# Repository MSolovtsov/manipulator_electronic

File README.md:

# Электроника манипулятора для лабораторных работ

Подпроект «Электроника» проекта «Манипулятор для лабораторных работ». Подключён как Git submodule
к родительскому репозиторию `educational-manipulator`.

## Состав электроники

Архитектура: контроллер ESP32-S3 (связь с ПК по USB); четыре канала привода
M1…M4 в основании — коллекторные ДПТ 24 В с драйвером, реле отключения,
датчиком тока и I2C-энкодером через мультиплексор (M1 — поворот платформы,
M2…M4 — звенья через токосъёмное кольцо); съёмный схват M5 с собственной
электроникой по UART; два режима работы — полный (от ESP32) и лабораторный
(управление звеном с внешнего разъёма), переключаемые кнопкой KH; питание от
внешнего адаптера 24 В с гальванической развязкой логики от силовой части.

Конкретные компоненты, их статусы (утверждено / предложение / уточняется),
спорные пункты и цены — в базе компонентов **`bom/Component_Base.xlsx`**
(листы «Компоненты», «Модули», «Отклонено», «Сводка», «Справочники»).
Текстовые копии листов для просмотра диффов — `bom/csv/`, обновляются
скриптом `scripts/export_component_base.py`.

Не определены: число степеней свободы, грузоподъёмность, двигатели, состав и
число плат. Исходные данные — концепт на доске Miro.

| Плата | Назначение | Кол-во | Текущая ревизия |
|-------|-----------|--------|-----------------|
| CH | Плата силовой части: развязка, драйвер, реле отключения, датчик тока, реле режима | 4 | — |
| MC | Плата микроконтроллера: ESP32-S3, мультиплексор I2C, оптореле KH, концевик M1, UART схвата, разъёмы CH | 1 | — |
| PS | Плата питания: реле шины 24 В, TVS, XL4015E, изолированный DC-DC острова, раздача +24 | 1 | — |
| LR | Плата режима ЛР: клеммы M1…M4, защита, PCF8574 и индикаторы звеньев | 1 | — |
| GR | Электроника схвата (по ТЗ на схват) | 1 | — |

Обоснование разделения, состав и связи между платами —
`docs/board-partition.md`. Плата CH проектируется после выбора двигателя
(от него зависят драйвер и реле отключения); MC, PS и LR — не ждут.

## Структура репозитория

```
electronics/
├── lib/            общие библиотеки KiCad для всех плат
│   ├── symbols/    символы (*.kicad_sym)
│   ├── footprints/ посадочные места (*.pretty/)
│   └── 3dmodels/   3D-модели компонентов (*.step, *.wrl) — только используемые в проекте
├── boards/         KiCad-проекты; один каталог = одна плата
│   └── <плата>/
│       └── release/<rev>/   замороженные выходные файлы изготовленной ревизии
├── system/         уровень системы: структурная схема, распиновка разъёмов
│   └── wiring/     схема соединений между платами, жгуты, кабели
├── calc/           расчёты: питание, токи, тепловой режим
├── bom/            база компонентов Component_Base.xlsx + csv/ для диффов
├── docs/           обоснование выбора приводов, датчиков, контроллера
└── scripts/        скрипты экспорта и проверки (export_component_base.py)
```

В репозиторий попадают исходники KiCad (`*.kicad_pro`, `*.kicad_sch`, `*.kicad_pcb`),
таблицы библиотек проекта (`sym-lib-table`, `fp-lib-table`), содержимое `lib/` и
каталоги `release/`. Резервные копии, автосохранения, локальные настройки вида
и пересоздаваемые выходные файлы (Gerber, отчёты DRC/ERC) не хранятся — см. `.gitignore`.

## Инструменты

- KiCad: **10.0**. Форматы файлов между мажорными версиями несовместимы,
  поэтому все участники работают в одной мажорной версии; она фиксируется здесь
  и не меняется в течение ревизии платы.
- `kicad-cli` — для экспорта схем, BOM и Gerber из скриптов в `scripts/`.

## Как открыть проект

Открыть `boards/<плата>/<плата>.kicad_pro` в KiCad. Библиотеки подключены через
таблицы проекта относительным путём `${KIPRJMOD}/../../lib/...`, глобальная
настройка путей не требуется.

Если KiCad сообщает об отсутствующих библиотеках:
1. проверить, что репозиторий склонирован целиком и каталог `lib/` не пуст;
2. проверить, что проект открыт из своего каталога в `boards/`, а не из копии;
3. убедиться, что версия KiCad соответствует указанной в разделе «Инструменты».

## Ревизии и выпуск

Ревизия платы записывается в поле `Rev` титульного блока схемы и выносится на
шёлкографию платы. Формат: `<код платы>-<ревизия>`, например `MC-A1`; код платы
задаётся при создании проекта платы.

На каждую ревизию, отправленную в производство, ставится Git-тег вида
`<плата>/<ревизия>`. Родительский репозиторий фиксирует коммит этого подпроекта,
поэтому по тегу родительского репозитория однозначно восстанавливается набор
ревизий всех плат конкретной версии манипулятора.

В `boards/<плата>/release/<rev>/` сохраняются выходные файлы изготовленной ревизии:
Gerber и drill, BOM, файл позиций компонентов, PDF схемы. Они соответствуют
физически существующей плате и не пересоздаются. Экспорт выполняется скриптом
из `scripts/` (команда уточняется после появления скрипта).

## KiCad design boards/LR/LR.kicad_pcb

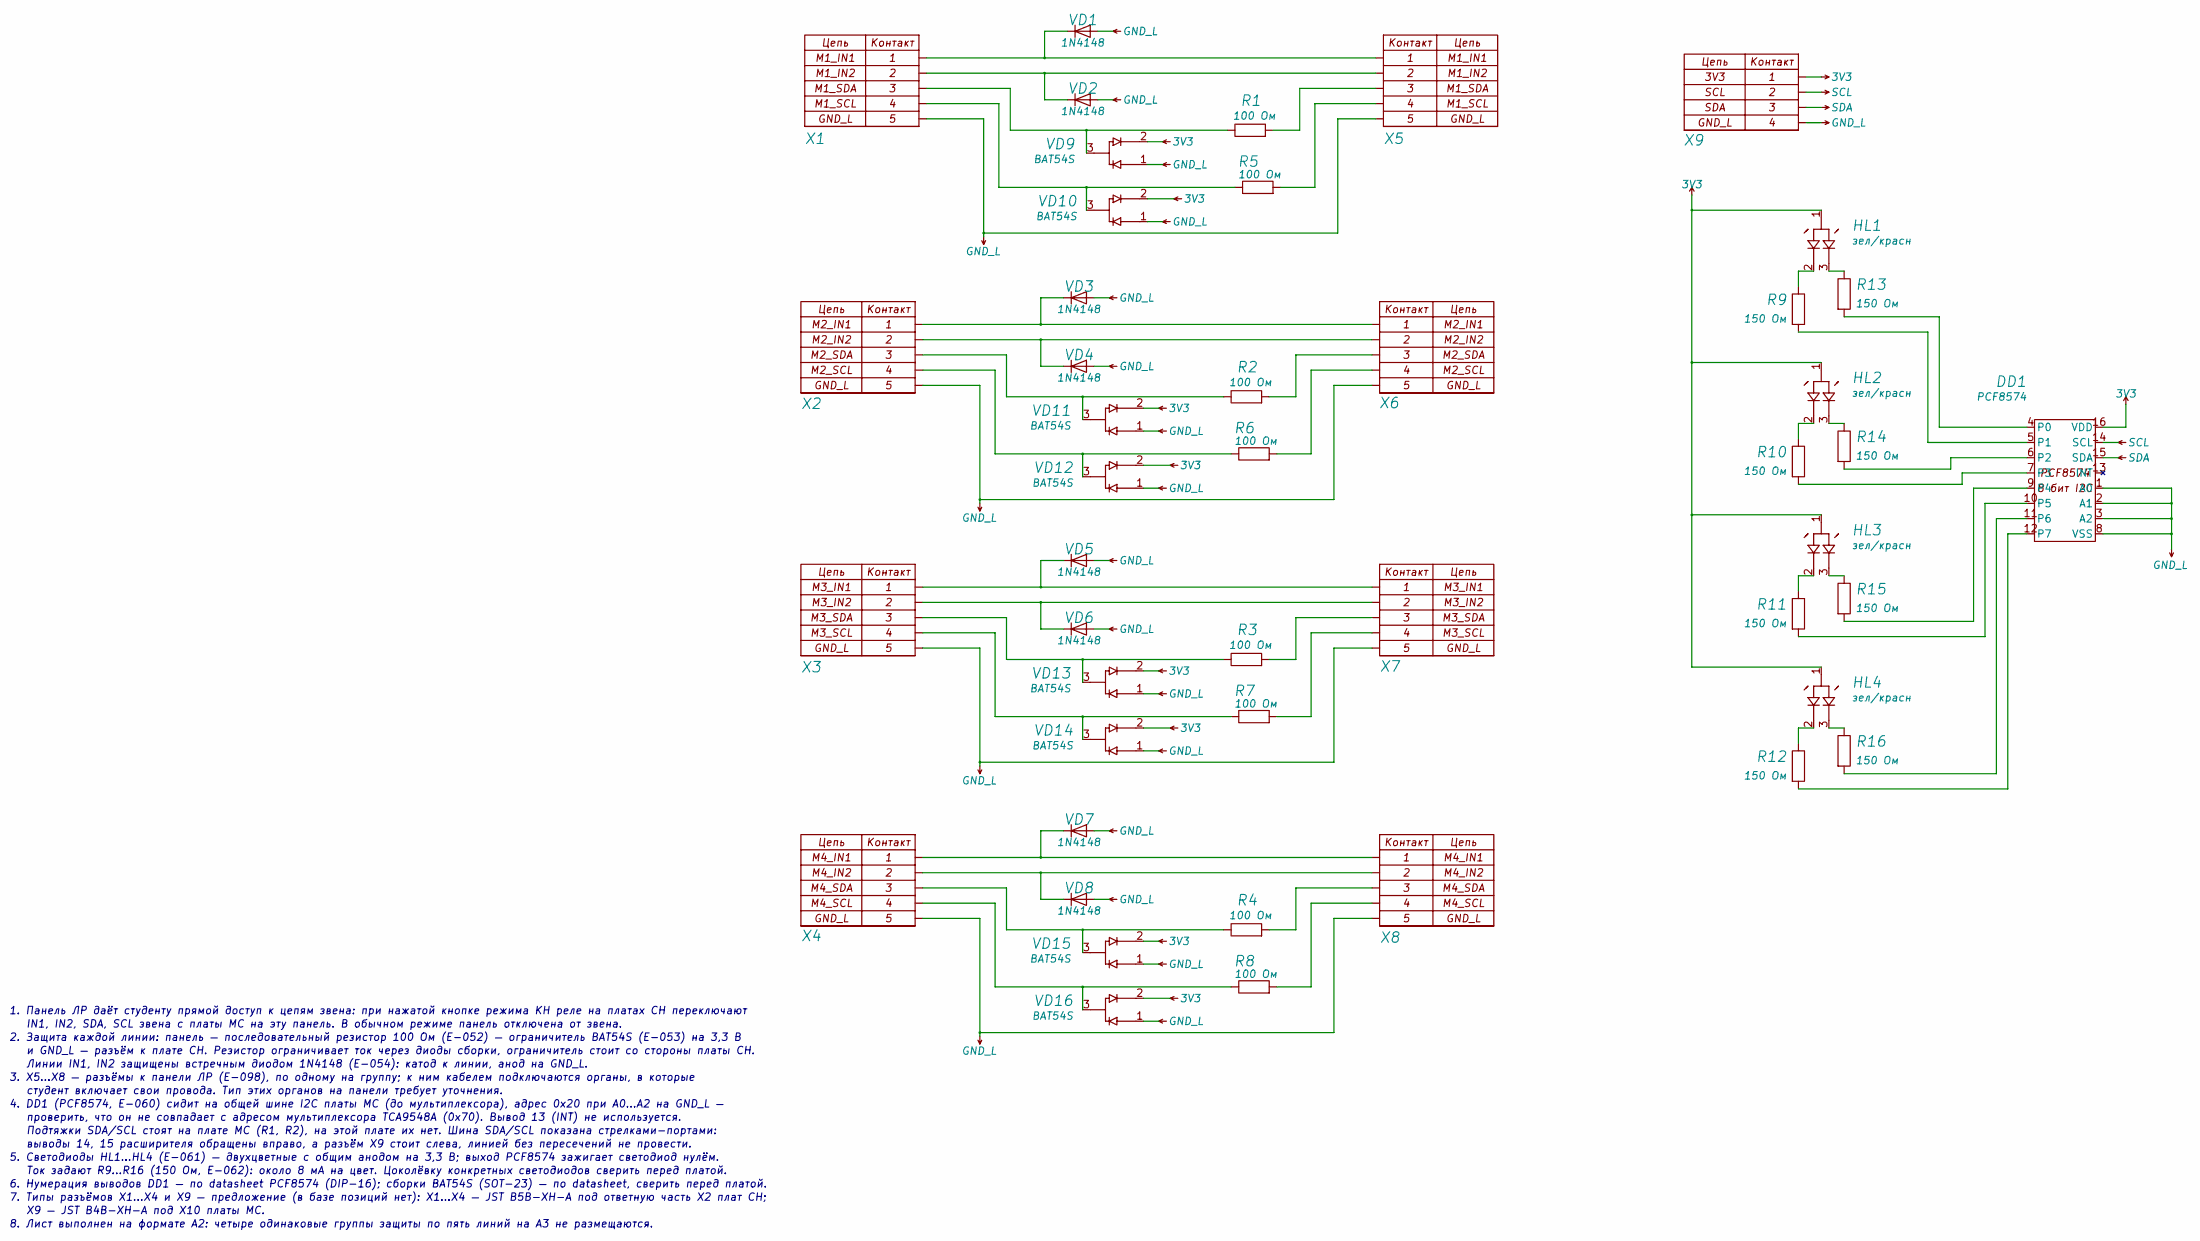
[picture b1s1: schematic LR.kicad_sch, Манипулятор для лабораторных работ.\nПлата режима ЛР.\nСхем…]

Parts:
DD1: PCF8574; DIP-16_W7.62mm
HL1, HL2, HL3, HL4: зел/красн; LED_Bicolor_5mm
R1, R2, R3, R4, R5, R6, R7, R8: 100 Ом; R_Axial_P10.16mm_V
R9, R10, R11, R12, R13, R14, R15, R16: 150 Ом; R_Axial_P10.16mm_V
VD1, VD2, VD3, VD4, VD5, VD6, VD7, VD8: 1N4148; D_DO-35_P7.62mm
VD9, VD10, VD11, VD12, VD13, VD14, VD15, VD16: BAT54S; SOT-23
X1, X2, X3, X4, X5, X6, X7, X8: B5B-XH-A; JST_XH_B5B-XH-A_L
X9: B4B-XH-A; JST_XH_B4B-XH-A_R

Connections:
3V3: DD1.16 (VDD), HL1.1 (A), HL2.1 (A), HL3.1 (A), HL4.1 (A), VD9.2 (K), VD10.2 (K), VD11.2 (K), VD12.2 (K), VD13.2 (K), VD14.2 (K), VD15.2 (K), VD16.2 (K), X9.1 (3V3)
GND_L: DD1.1 (A0), DD1.2 (A1), DD1.3 (A2), DD1.8 (VSS), VD1.2 (A), VD2.2 (A), VD3.2 (A), VD4.2 (A), VD5.2 (A), VD6.2 (A), VD7.2 (A), VD8.2 (A), VD9.1 (A), VD10.1 (A), VD11.1 (A), VD12.1 (A), VD13.1 (A), VD14.1 (A), VD15.1 (A), VD16.1 (A), X1.5 (GND_L), X2.5 (GND_L), X3.5 (GND_L), X4.5 (GND_L), X5.5 (GND_L), X6.5 (GND_L), X7.5 (GND_L), X8.5 (GND_L), X9.4 (GND_L)
unnamed: DD1.4 (P0), R13.2
unnamed: DD1.5 (P1), R9.2
unnamed: DD1.6 (P2), R14.2
unnamed: DD1.7 (P3), R10.2
unnamed: DD1.9 (P4), R15.2
unnamed: DD1.10 (P5), R11.2
unnamed: DD1.11 (P6), R16.2
unnamed: DD1.12 (P7), R12.2
unnamed: HL1.2 (K1), R9.1
unnamed: HL1.3 (K2), R13.1
unnamed: HL2.2 (K1), R10.1
unnamed: HL2.3 (K2), R14.1
unnamed: HL3.2 (K1), R11.1
unnamed: HL3.3 (K2), R15.1
unnamed: HL4.2 (K1), R12.1
unnamed: HL4.3 (K2), R16.1
unnamed: VD1.1 (K), X1.1 (M1_IN1), X5.1 (M1_IN1)
unnamed: VD2.1 (K), X1.2 (M1_IN2), X5.2 (M1_IN2)
unnamed: VD3.1 (K), X2.1 (M2_IN1), X6.1 (M2_IN1)
unnamed: VD4.1 (K), X2.2 (M2_IN2), X6.2 (M2_IN2)
unnamed: VD5.1 (K), X3.1 (M3_IN1), X7.1 (M3_IN1)
unnamed: VD6.1 (K), X3.2 (M3_IN2), X7.2 (M3_IN2)
unnamed: VD7.1 (K), X4.1 (M4_IN1), X8.1 (M4_IN1)
unnamed: VD8.1 (K), X4.2 (M4_IN2), X8.2 (M4_IN2)
unnamed: R1.1, VD9.3 (IN), X1.3 (M1_SDA)
unnamed: R5.1, VD10.3 (IN), X1.4 (M1_SCL)
unnamed: R2.1, VD11.3 (IN), X2.3 (M2_SDA)
unnamed: R6.1, VD12.3 (IN), X2.4 (M2_SCL)
unnamed: R3.1, VD13.3 (IN), X3.3 (M3_SDA)
unnamed: R7.1, VD14.3 (IN), X3.4 (M3_SCL)
unnamed: R4.1, VD15.3 (IN), X4.3 (M4_SDA)
unnamed: R8.1, VD16.3 (IN), X4.4 (M4_SCL)
unnamed: R5.2, X5.4 (M1_SCL)
unnamed: R1.2, X5.3 (M1_SDA)
unnamed: R6.2, X6.4 (M2_SCL)
unnamed: R2.2, X6.3 (M2_SDA)
unnamed: R7.2, X7.4 (M3_SCL)
unnamed: R3.2, X7.3 (M3_SDA)
unnamed: R8.2, X8.4 (M4_SCL)
unnamed: R4.2, X8.3 (M4_SDA)
SCL: DD1.14 (SCL), X9.2 (SCL)
SDA: DD1.15 (SDA), X9.3 (SDA)

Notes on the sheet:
Линии IN1, IN2 защищены встречным диодом 1N4148 (E-054): катод к линии, анод на GND_L.
2. Защита каждой линии: панель — последовательный резистор 100 Ом (E-052) — ограничитель BAT54S (E-053) на 3,3 В
IN1, IN2, SDA, SCL звена с платы MC на эту панель. В обычном режиме панель отключена от звена.
3. X5…X8 — разъёмы к панели ЛР (E-098), по одному на группу; к ним кабелем подключаются органы, в которые
Ток задают R9…R16 (150 Ом, E-062): около 8 мА на цвет. Цоколёвку конкретных светодиодов сверить перед платой.
X9 — JST B4B-XH-A под X10 платы MC.
проверить, что он не совпадает с адресом мультиплексора TCA9548A (0x70). Вывод 13 (INT) не используется.
7. Типы разъёмов X1…X4 и X9 — предложение (в базе позиций нет): X1…X4 — JST B5B-XH-A под ответную часть X2 плат CH;
5. Светодиоды HL1…HL4 (E-061) — двухцветные с общим анодом на 3,3 В; выход PCF8574 зажигает светодиод нулём.
1. Панель ЛР даёт студенту прямой доступ к цепям звена: при нажатой кнопке режима KH реле на платах CH переключают
выводы 14, 15 расширителя обращены вправо, а разъём X9 стоит слева, линией без пересечений не провести.
8. Лист выполнен на формате A2: четыре одинаковые группы защиты по пять линий на A3 не размещаются.
студент включает свои провода. Тип этих органов на панели требует уточнения.
Подтяжки SDA/SCL стоят на плате MC (R1, R2), на этой плате их нет. Шина SDA/SCL показана стрелками-портами:
и GND_L — разъём к плате CH. Резистор ограничивает ток через диоды сборки, ограничитель стоит со стороны платы CH.
6. Нумерация выводов DD1 — по datasheet PCF8574 (DIP-16); сборки BAT54S (SOT-23) — по datasheet, сверить перед платой.
4. DD1 (PCF8574, E-060) сидит на общей шине I2C платы MC (до мультиплексора), адрес 0x20 при A0…A2 на GND_L —

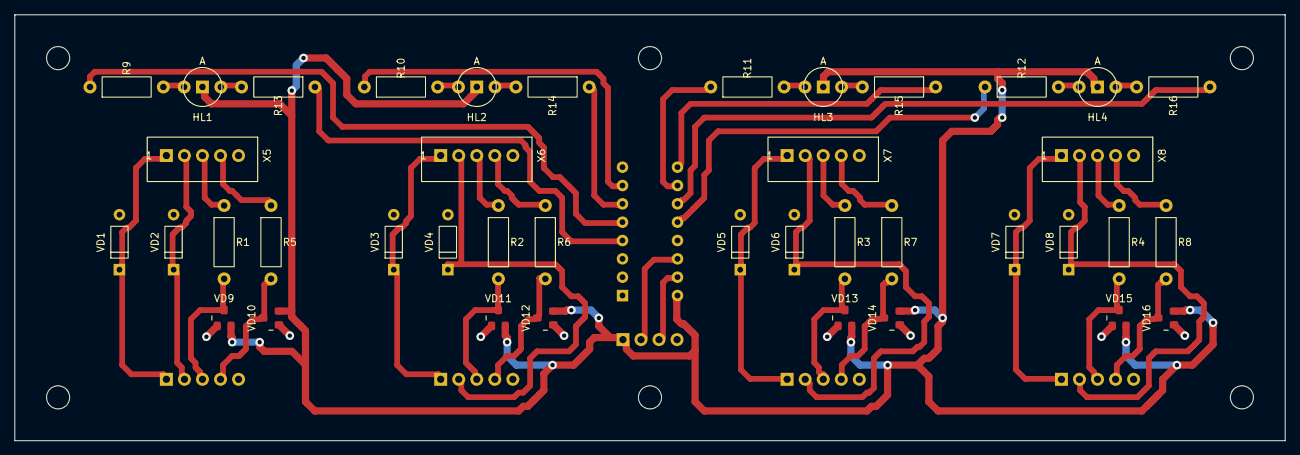
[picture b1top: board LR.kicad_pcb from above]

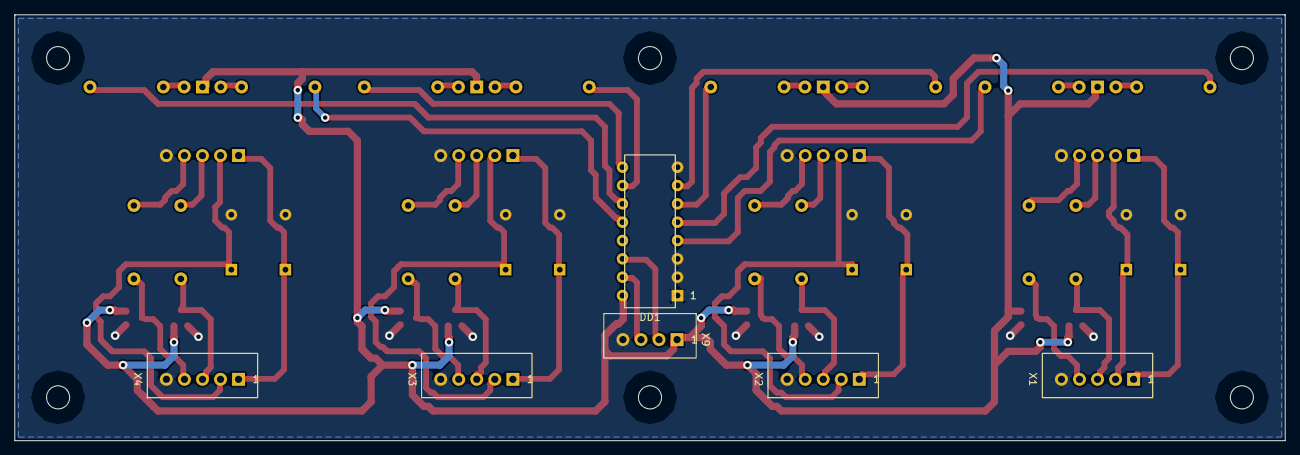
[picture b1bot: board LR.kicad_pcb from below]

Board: 2 copper layers, 176.0 x 59.0 mm, 52 parts (6 on the bottom side), 44 nets.

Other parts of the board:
H1, H2, H3, H4, H5, H6: M3; MountingHole_3.2mm_M3

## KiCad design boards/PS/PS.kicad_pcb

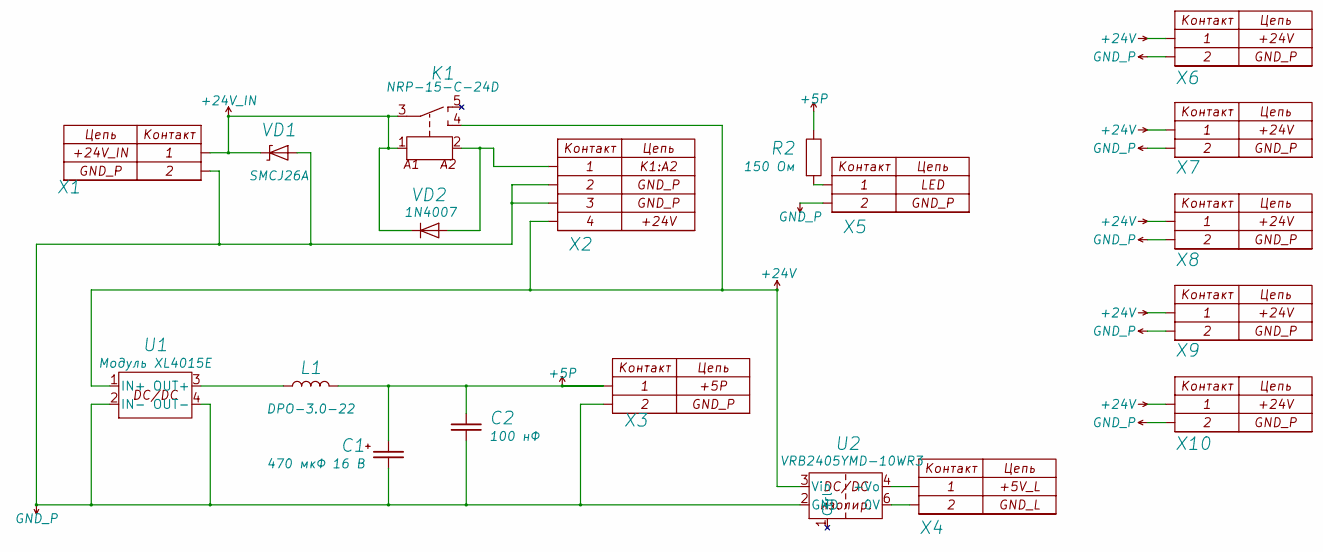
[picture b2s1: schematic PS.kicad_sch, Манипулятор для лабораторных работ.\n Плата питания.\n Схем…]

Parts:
C1: 470 мкФ 16 В; CP_Radial_D8.0mm_P3.50mm
C2: 100 нФ; C_Disc_P5.00mm
K1: NRP-15-C-24D; Relay_NRP-15_1C
L1: DPO-3.0-22; L_Toroid_D20_P10.16mm
R2: 150 Ом; R_Axial_P10.16mm_V
U1: Модуль XL4015E; Module_XL4015E_zone
U2: VRB2405YMD-10WR3; DCDC_Mornsun_YMD_25.4x25.4
VD1: SMCJ26A; D_SMC
VD2: 1N4007; D_DO-41_P10.16mm
X1: DG301-5.0-02P-12; TB_DG301-5.0_2P
X2: B4B-XH-A; JST_XH_B4B-XH-A
X3, X4: B2P-VH; JST_VH_B2P-VH_V
X5: B2B-XH-A; JST_XH_B2B-XH-A
X6, X7, X8, X9, X10: DG301-5.0-02P-12; TB_DG301-5.0_2P_V

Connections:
+5P: C1.1, C2.1, L1.2, R2.1, X3.1 (+5P)
+24V: K1.4 (NO), U1.1 (IN+), U2.3 (Vin), X2.4 (+24V), X6.1 (+24V), X7.1 (+24V), X8.1 (+24V), X9.1 (+24V), X10.1 (+24V)
+24V_IN: K1.1 (A1), K1.3 (COM), VD1.1 (K), VD2.1 (K), X1.1 (+24V_IN)
GND_P: C1.2, C2.2, U1.2 (IN-), U1.4 (OUT-), U2.2 (GND), VD1.2 (A), X1.2 (GND_P), X2.2 (GND_P), X2.3 (GND_P), X3.2 (GND_P), X5.2 (GND_P), X6.2 (GND_P), X7.2 (GND_P), X8.2 (GND_P), X9.2 (GND_P), X10.2 (GND_P)
unnamed: K1.2 (A2), VD2.2 (A), X2.1 (K1:A2)
unnamed: L1.1, U1.3 (OUT+)
unnamed: U2.6 (0V), X4.2 (GND_L)
unnamed: U2.4 (+Vo), X4.1 (+5V_L)
unnamed: R2.2, X5.1 (LED)

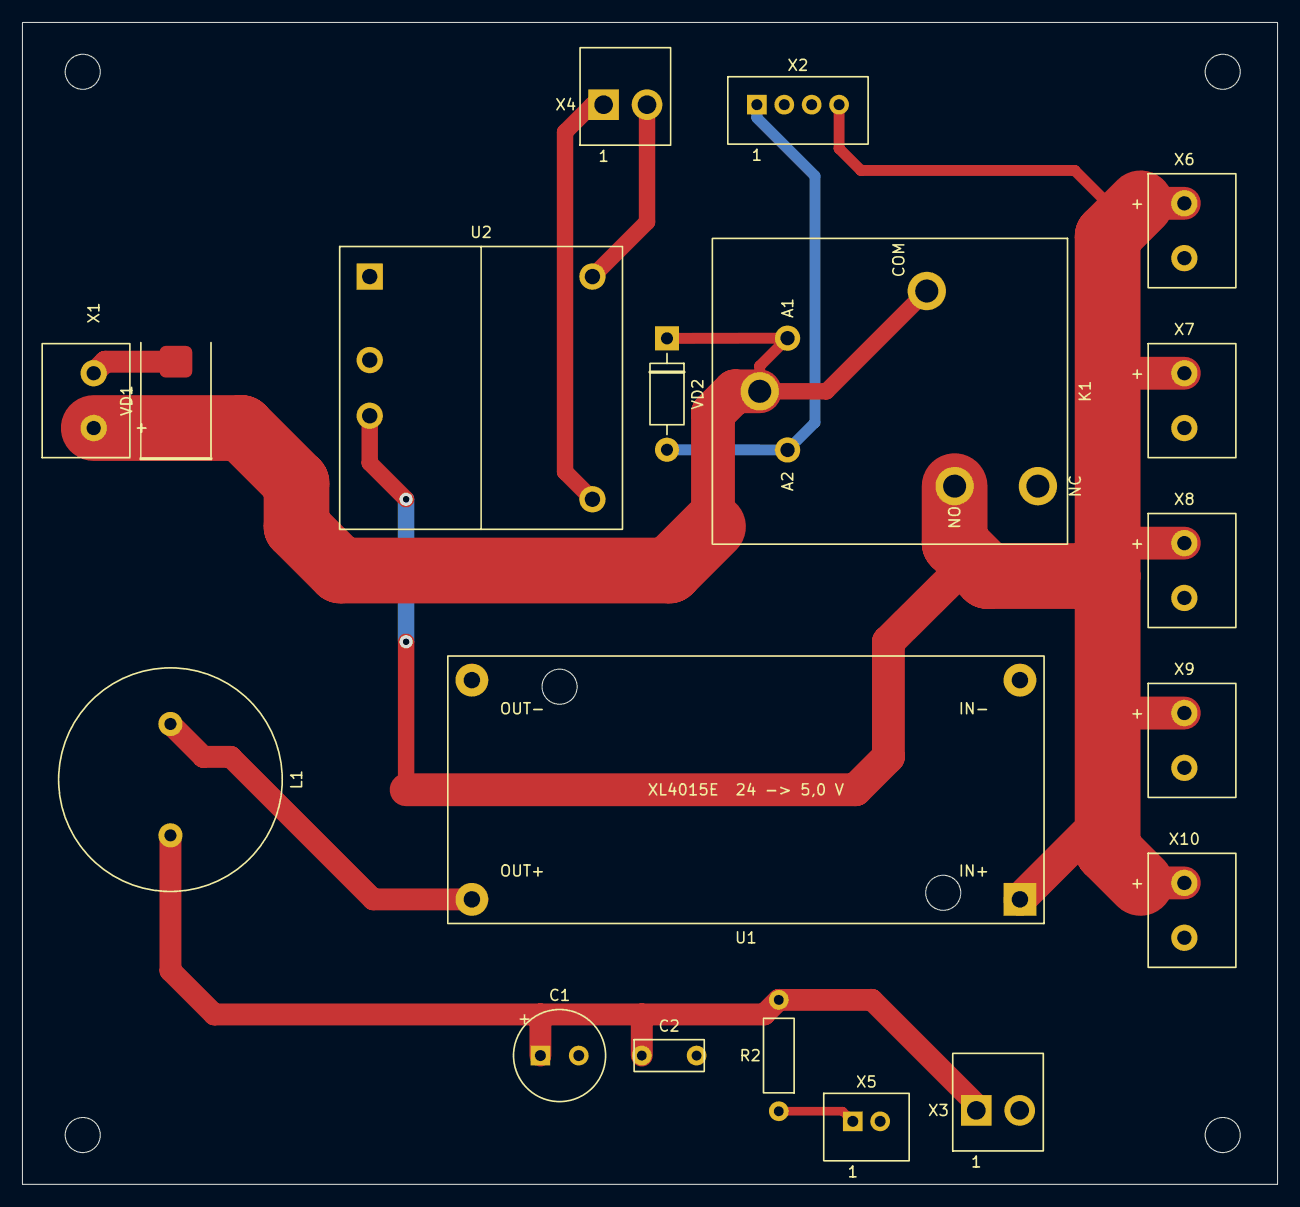
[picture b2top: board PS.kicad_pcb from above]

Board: 2 copper layers, 114.5 x 106.0 mm, 23 parts (0 on the bottom side), 9 nets.

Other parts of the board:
H1, H2, H3, H4: M3; MountingHole_3.2mm_M3

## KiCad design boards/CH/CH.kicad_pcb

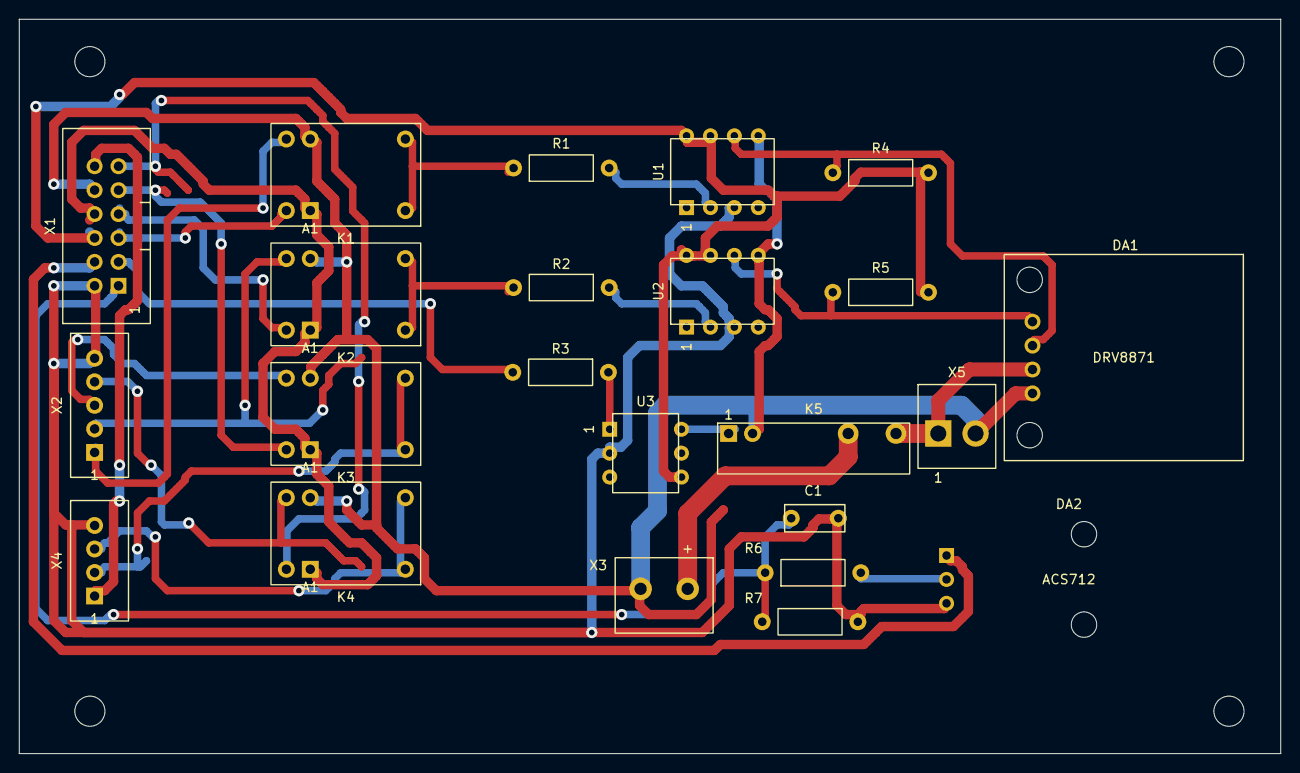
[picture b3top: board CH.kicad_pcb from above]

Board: 2 copper layers, 134.0 x 78.0 mm, 27 parts (0 on the bottom side), 29 nets.

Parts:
C1: 100 нФ; C_Disc_P5.00mm
DA1: DRV8871; Module_DRV8871
DA2: ACS712-20A; Module_ACS712
H1, H2, H3, H4: M3; MountingHole_3.2mm_M3
K1, K2, K3, K4: NRP-02-C-05DH; Relay_NRP-02_1C
K5: HF49FD/005-1H11; Relay_HF49FD_1A
R1, R2: 220 Ом; R_Axial_P10.16mm_V
R3: 150 Ом; R_Axial_P10.16mm_V
R4, R5: 4,7 кОм; R_Axial_P10.16mm_V
R6: 10 кОм; R_Axial_P10.16mm_V
R7: 20 кОм; R_Axial_P10.16mm_V
U1, U2: 6N137; DIP-8_W7.62mm
U3: КР293КП2Б; DIP-6_W7.62mm
X1: BH-12 (2×6); IDC-Header_2x06_P2.54mm_Vertical_D
X2: B5B-XH-A; JST_XH_B5B-XH-A_L
X3: DG301-5.0-02P; TB_DG301-5.0_2P_V
X4: B4B-XH-A; JST_XH_B4B-XH-A_L
X5: B2P-VH; JST_VH_B2P-VH

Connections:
3V3: X1.12 (3V3), X4.1 (3V3)
+5P: R4.1, R5.1, U1.7 (VE), U1.8 (VCC), U2.7 (VE), U2.8 (VCC), U3.4 (OUT), X1.6 (+5P)
+5V_L: DA2.1, X1.4 (+5V_L)
+24V: K5.3, X3.1 (+24V)
+24V_M: DA1.1, K5.4, X5.1
CURR: C1.1, R6.2, R7.1, X1.1 (CURR)
GND_L: C1.2, DA2.3, R7.2, U1.3 (K), U2.3 (K), U3.2 (K), X1.2 (GND_L), X2.5 (GND_L), X4.4 (GND_L)
GND_P: DA1.2, K1.2, K2.2, K3.2, K4.2, K5.2, U1.5 (GND), U2.5 (GND), X1.10 (GND_P), X3.2 (GND_P), X5.2
IN1_LR: K1.4, X2.1 (IN1_LR)
IN2_LR: K2.4, X2.2 (IN2_LR)
KH: K1.1, K2.1, K3.1, K4.1, X1.8 (KH)
unnamed: DA1.3, R4.2, U1.6 (VO)
unnamed: DA1.4, R5.2, U2.6 (VO)
unnamed: DA2.2, R6.1
unnamed: K1.3, R1.2
unnamed: K1.5, X1.5 (IN1)
unnamed: K2.3, R2.1
unnamed: K2.5, X1.7 (IN2)
unnamed: K3.3, X4.2 (SDA)
unnamed: K3.5, X1.9 (SDA)
unnamed: K4.3, X4.3 (SCL)
unnamed: K4.5, X1.11 (SCL)
unnamed: K5.1, U3.6 (OUT)
unnamed: R1.1, U1.2 (A)
unnamed: R2.2, U2.2 (A)
unnamed: R3.2, U3.1 (A)
RELE: R3.1, X1.3 (RELE)
SCL_LR: K4.4, X2.4 (SCL_LR)
SDA_LR: K3.4, X2.3 (SDA_LR)

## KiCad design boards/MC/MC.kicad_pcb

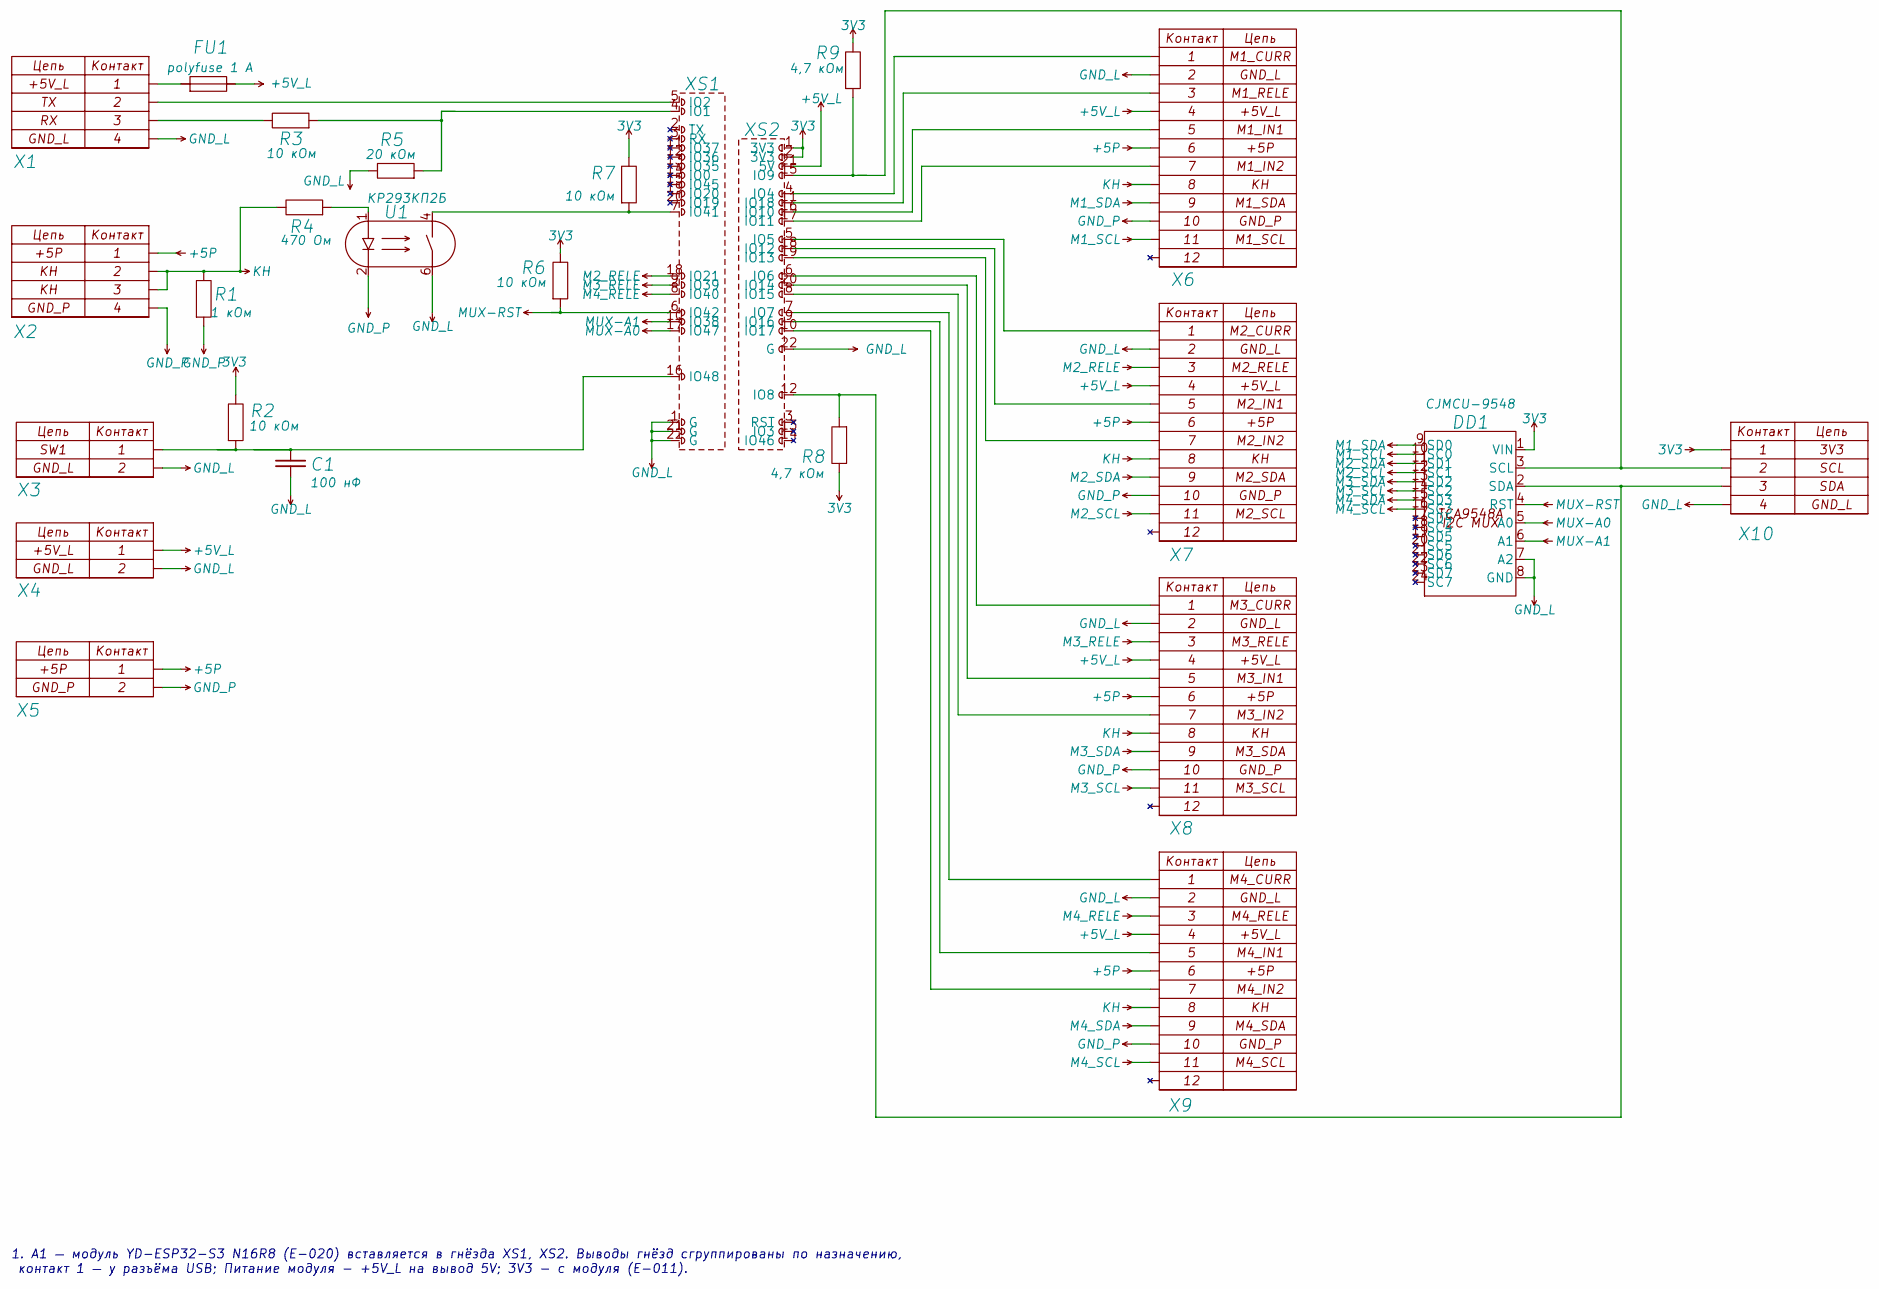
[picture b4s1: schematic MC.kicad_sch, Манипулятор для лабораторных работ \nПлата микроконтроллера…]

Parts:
C1: 100 нФ; C_Disc_P5.00mm
DD1: CJMCU-9548; Module_CJMCU-9548
FU1: polyfuse 1 А; Fuse_PTC_Radial_P5.08mm
R1: 1 кОм; R_Axial_P10.16mm_V
R2, R3, R7: 10 кОм; R_Axial_P10.16mm_V
R4: 470 Ом; R_Axial_P10.16mm_V
R5: 20 кОм; R_Axial_P10.16mm_V
R6: 10 кОм; R_Axial_P10.16mm
R8, R9: 4,7 кОм; R_Axial_P10.16mm
U1: КР293КП2Б; DIP-6_W7.62mm_H
X1, X2: B4B-XH-A; JST_XH_B4B-XH-A_L
X3: B2B-XH-A; JST_XH_B2B-XH-A_L
X4, X5: DG301-5.0-02P; TB_DG301-5.0_2P_R
X6, X7, X8, X9: BH-12 (2×6); IDC-Header_2x06_P2.54mm_Vertical
X10: B4B-XH-A; JST_XH_B4B-XH-A_R
XS1, XS2: PBS-22; PinSocket_1x22_P2.54mm_Vertical

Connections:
3V3: DD1.1 (VIN), R2.1, R6.1, R7.1, R8.1, R9.1, X10.1 (3V3), XS2.1 (3V3), XS2.2 (3V3)
+5P: X2.1 (+5P), X5.1 (+5P), X6.6 (+5P), X7.6 (+5P), X8.6 (+5P), X9.6 (+5P)
+5V_L: FU1.2, X4.1 (+5V_L), X6.4 (+5V_L), X7.4 (+5V_L), X8.4 (+5V_L), X9.4 (+5V_L), XS2.21 (5V)
GND_L: C1.2, DD1.7 (A2), DD1.8 (GND), R5.1, U1.6 (OUT), X1.4 (GND_L), X3.2 (GND_L), X4.2 (GND_L), X6.2 (GND_L), X7.2 (GND_L), X8.2 (GND_L), X9.2 (GND_L), X10.4 (GND_L), XS1.1 (G), XS1.21 (G), XS1.22 (G), XS2.22 (G)
GND_P: R1.2, U1.2 (K), X2.4 (GND_P), X5.2 (GND_P), X6.10 (GND_P), X7.10 (GND_P), X8.10 (GND_P), X9.10 (GND_P)
KH: R1.1, R4.1, X2.2 (KH), X2.3 (KH), X6.8 (KH), X7.8 (KH), X8.8 (KH), X9.8 (KH)
M1_SCL: DD1.10 (SC0), X6.11 (M1_SCL)
M1_SDA: DD1.9 (SD0), X6.9 (M1_SDA)
M2_RELE: X7.3 (M2_RELE), XS1.18 (IO21)
M2_SCL: DD1.12 (SC1), X7.11 (M2_SCL)
M2_SDA: DD1.11 (SD1), X7.9 (M2_SDA)
M3_RELE: X8.3 (M3_RELE), XS1.9 (IO39)
M3_SCL: DD1.14 (SC2), X8.11 (M3_SCL)
M3_SDA: DD1.13 (SD2), X8.9 (M3_SDA)
M4_RELE: X9.3 (M4_RELE), XS1.8 (IO40)
M4_SCL: DD1.16 (SC3), X9.11 (M4_SCL)
M4_SDA: DD1.15 (SD3), X9.9 (M4_SDA)
MUX-A0: DD1.5 (A0), XS1.17 (IO47)
MUX-A1: DD1.6 (A1), XS1.10 (IO38)
MUX-RST: DD1.4 (RST), R6.2, XS1.6 (IO42)
unnamed: DD1.3 (SCL), R9.2, X10.2 (SCL), XS2.15 (IO9)
unnamed: DD1.2 (SDA), R8.2, X10.3 (SDA), XS2.12 (IO8)
unnamed: R4.2, U1.1 (A)
unnamed: FU1.1, X1.1 (+5V_L)
unnamed: R3.1, X1.3 (RX)
unnamed: X1.2 (TX), XS1.5 (IO2)
unnamed: C1.1, R2.2, X3.1 (SW1), XS1.16 (IO48)
unnamed: X6.1 (M1_CURR), XS2.4 (IO4)
unnamed: X6.5 (M1_IN1), XS2.16 (IO10)
unnamed: X6.7 (M1_IN2), XS2.17 (IO11)
unnamed: X6.3 (M1_RELE), XS2.11 (IO18)
unnamed: X7.1 (M2_CURR), XS2.5 (IO5)
unnamed: X7.5 (M2_IN1), XS2.18 (IO12)
unnamed: X7.7 (M2_IN2), XS2.19 (IO13)
unnamed: X8.1 (M3_CURR), XS2.6 (IO6)
unnamed: X8.5 (M3_IN1), XS2.20 (IO14)
unnamed: X8.7 (M3_IN2), XS2.8 (IO15)
unnamed: X9.1 (M4_CURR), XS2.7 (IO7)
unnamed: X9.5 (M4_IN1), XS2.9 (IO16)
unnamed: X9.7 (M4_IN2), XS2.10 (IO17)
unnamed: R3.2, R5.2, XS1.4 (IO1)
unnamed: R7.2, U1.4 (OUT), XS1.7 (IO41)

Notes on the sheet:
1. A1 — модуль YD-ESP32-S3 N16R8 (E-020) вставляется в гнёзда XS1, XS2. Выводы гнёзд сгруппированы по назначению,
контакт 1 — у разъёма USB; Питание модуля - +5V_L на вывод 5V; 3V3 - с модуля (E-011).

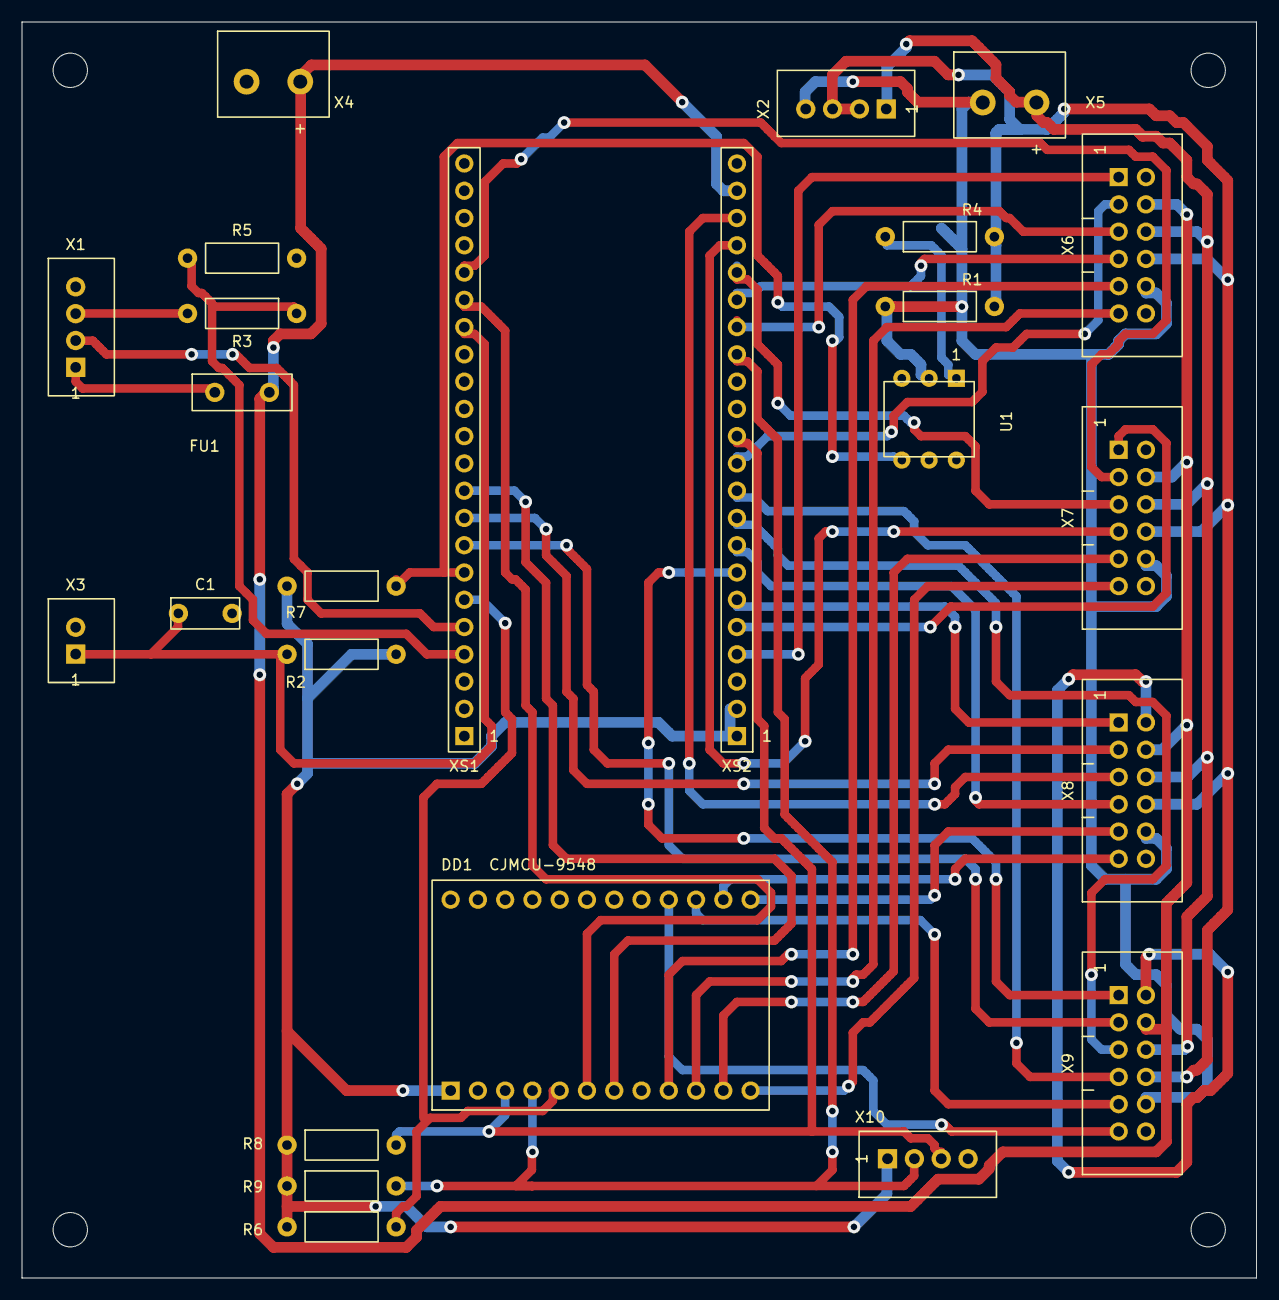
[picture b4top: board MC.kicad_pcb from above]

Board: 2 copper layers, 115.0 x 117.0 mm, 29 parts (0 on the bottom side), 42 nets.

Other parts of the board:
H1, H2, H3, H4: M3; MountingHole_3.2mm_M3
